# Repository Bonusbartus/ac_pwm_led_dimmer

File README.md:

# A PCB for dimming AC LED lamps

TODO

Not sure yet about (the placement of) the MAINS and LAMP connector.
Check if the optocoupler is fast enough. the ESP8266 has a PWM driver which can operate at 100-1000Hz.

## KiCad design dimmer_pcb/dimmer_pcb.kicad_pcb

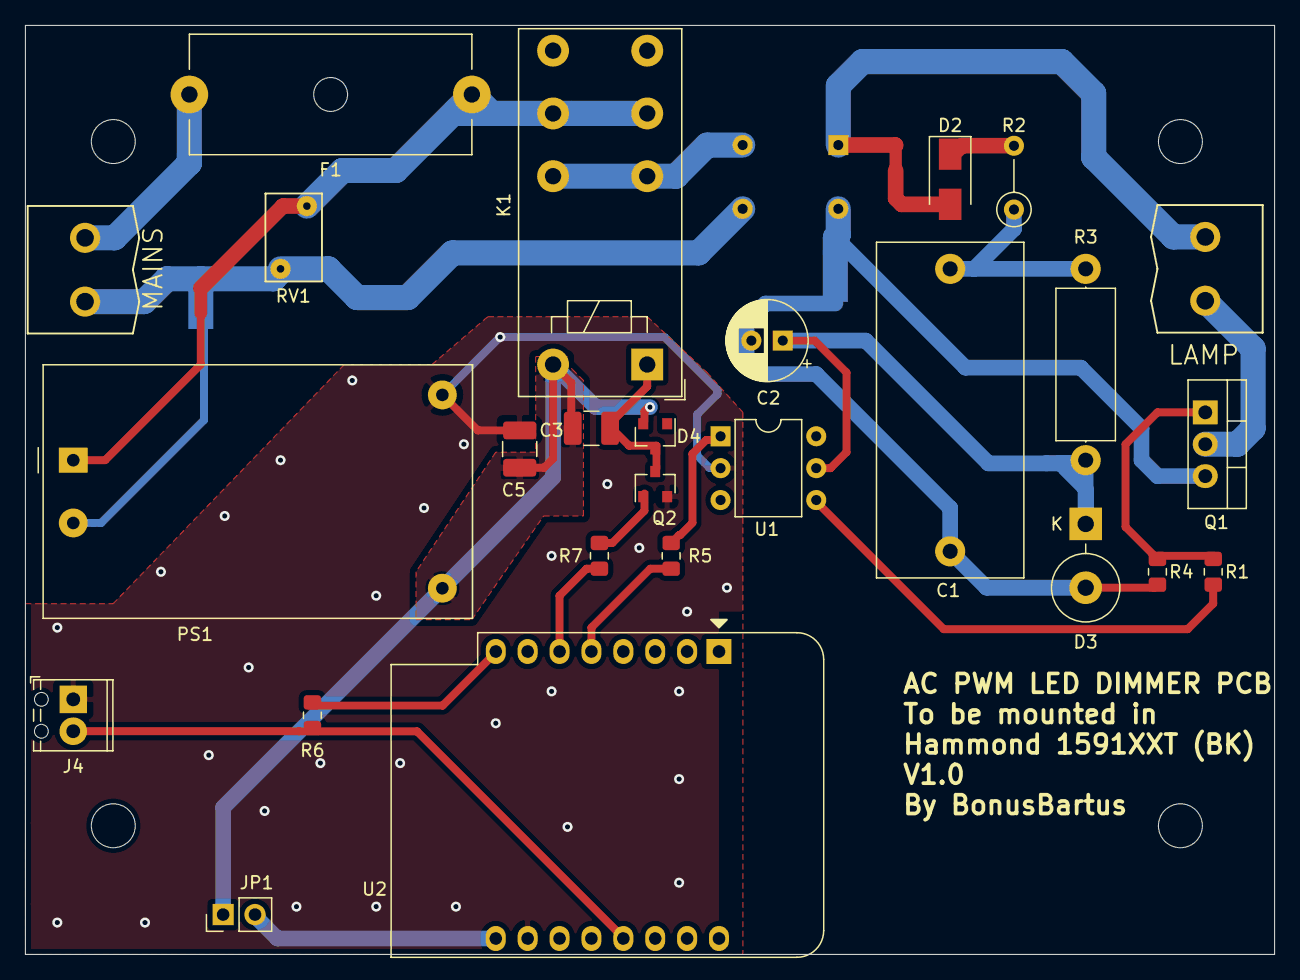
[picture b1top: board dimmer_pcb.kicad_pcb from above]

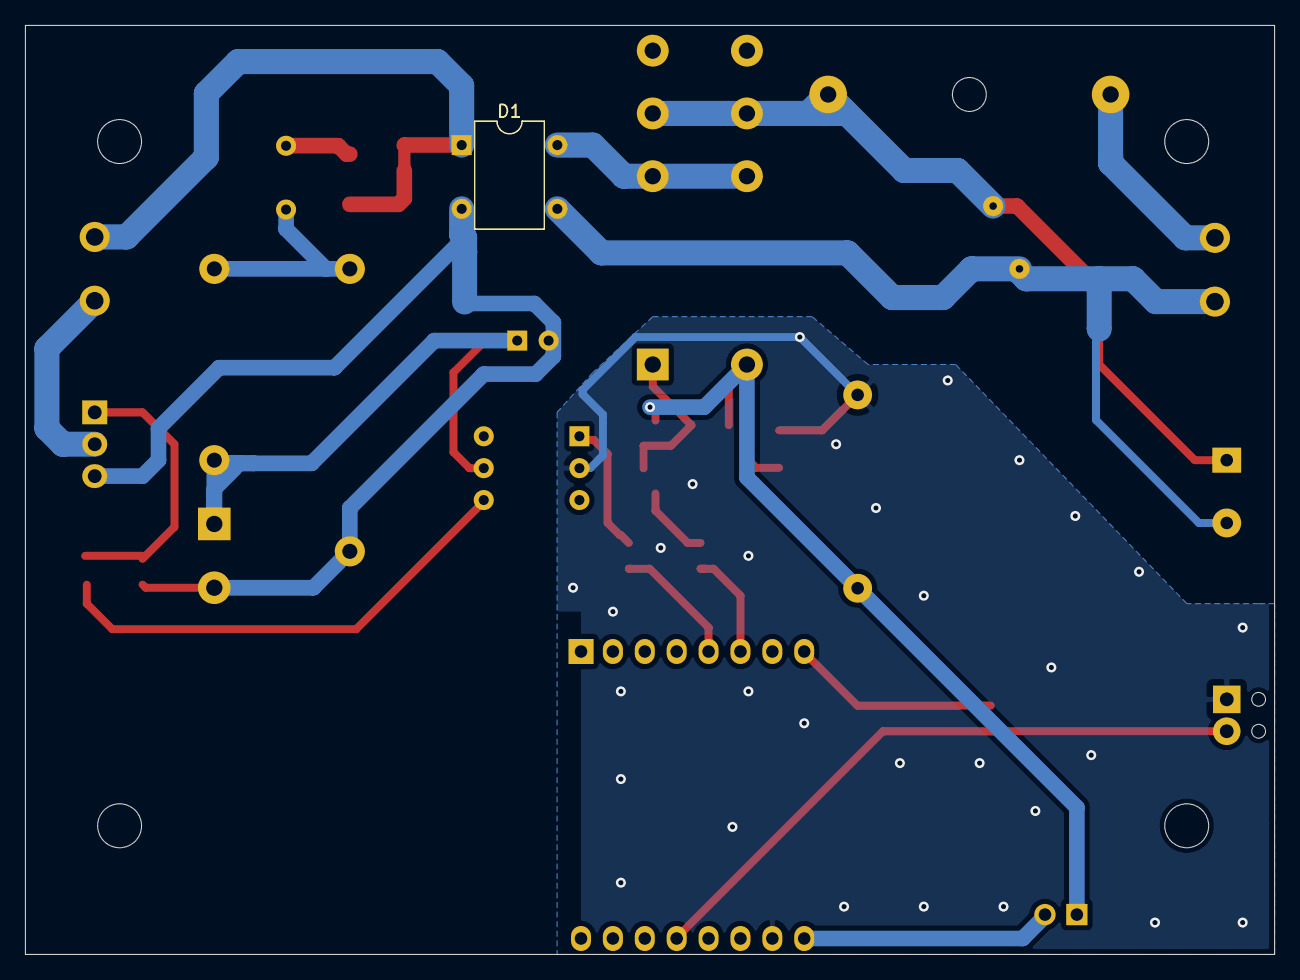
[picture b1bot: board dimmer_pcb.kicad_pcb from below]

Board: 2 copper layers, 99.5 x 74.0 mm, 35 parts (3 on the bottom side), 26 nets.

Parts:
C1: 220nF 760V; C_Rect_L26.5mm_W11.5mm_P22.50mm_MKS4
C2: 47uF; CP_Radial_D6.3mm_P2.50mm
C3: 100nF OPTIONAL; C_1210_3225Metric_Pad1.42x2.65mm_HandSolder
C5: 10uF; C_1210_3225Metric_Pad1.42x2.65mm_HandSolder
D1: DF10M; Diode_Bridge_DIP-4_W7.62mm_P5.08mm
D2: MRA4007T3G; D_SMA
D3: 1N5352BG 15V 5Watt; D_DO-201_P5.08mm_Vertical_KathodeUp
D4: BAV99; SOT-23
F1: 1A SB; Fuseholder_Cylinder-5x20mm_Schurter_0031_8201_Horizontal_Op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
H1, H2, H3, H4: MountingHole 3.5mm; MountingHole_3.5mm
J1: LAMP; Weidmuller-SL-5.08-Vertical-2Pole
J2: MAINS; Weidmuller-SL-5.08-Vertical-2Pole
J4: Switch; TerminalBlock_Phoenix_MPT-0,5-2-2.54_1x02_P2.54mm_Horizontal
JP1: Jumper; PinHeader_1x02_P2.54mm_Vertical
K1: G5RLE-1; Relay_SPDT_Omron_G5RL-1-E
NT1, NT3: Net-Tie_2; NetTie-2_SMD_Pad1.0mm
NT2, NT4: Net-Tie_2; NetTie-2_SMD_Pad2.0mm
PS1: HLK-PM01; Converter_ACDC_HiLink_HLK-PMxx
Q1: IRF740; TO-220-3_Vertical
Q2: BC847; SOT-23
R1, R5: 220; R_0805_2012Metric_Pad1.15x1.40mm_HandSolder
R2: 220/0.5Watt; R_Axial_DIN0207_L6.3mm_D2.5mm_P5.08mm_Vertical
R3: 150k/2Watt; R_Axial_DIN0414_L11.9mm_D4.5mm_P15.24mm_Horizontal
R4: 6K8; R_0805_2012Metric_Pad1.15x1.40mm_HandSolder
R6: 10k; R_0805_2012Metric_Pad1.15x1.40mm_HandSolder
R7: 3k3; R_0805_2012Metric_Pad1.15x1.40mm_HandSolder
RV1: Varistor; RV_Disc_D7mm_W4.5mm_P5mm
U1: 4N35 (M by ON Semi ); DIP-6_W7.62mm
U2: WeMos_D1_mini; WEMOS_D1_mini_light

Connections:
5V: C3.1, C5.2, D4.2, JP1.1, K1.8, PS1.4
+3V3: R6.1, U2.8
D5: R7.2, U2.6
DC15V: C2.1, D3.1, R3.1, U1.5
GND: C5.1, J4.1, PS1.3, Q2.2, U1.2, U2.10
MAINS-AC-HP-L: F1.1, K1.3, K1.6, NT1.1, RV1.2
MAINS-AC-HP-L-FROM-RELAY: D1.4, K1.2, K1.7
MAINS-AC-HP-N: D1.3, J2.1, NT2.1, RV1.1
MAINS-AC-LP-L: NT1.2, PS1.1
MAINS-AC-LP-N: NT2.2, PS1.2
MAINS-DC-HP_+: D1.1, J1.1, NT3.1
MAINS-DC-HP_-: D1.2, NT4.1, Q1.3
MAINS-DC-LP_+: D2.2, NT3.2
MAINS-DC-LP_-: C1.2, C2.2, D3.2, NT4.2, R4.1
unnamed: C1.1, R2.1, R3.2
unnamed: C3.2, D4.3, K1.1, Q2.3
unnamed: D2.1, R2.2
unnamed: F1.2, J2.2
unnamed: J1.2, Q1.2
unnamed: J4.2, R6.2, U2.13
unnamed: JP1.2, U2.9
unnamed: Q1.1, R1.1, R4.2
unnamed: Q2.1, R7.1
unnamed: R5.1, U1.1
PWM: R5.2, U2.5
PWM-SIGNAL: R1.2, U1.4

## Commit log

2019-06-11 initial commmit, fixed according to review by Squantor: - Fixed Opto polatiry - removed capacitor C3 next to relay - rotated FET to make adding heatsink easier
    re-aligned components to 25mil grid
2019-06-11 added README.md text
2019-06-22 updated pcb, moved text to silkscreen cleaned up silkscreen moved traced to have a nicer layout switched rectifier bridge
